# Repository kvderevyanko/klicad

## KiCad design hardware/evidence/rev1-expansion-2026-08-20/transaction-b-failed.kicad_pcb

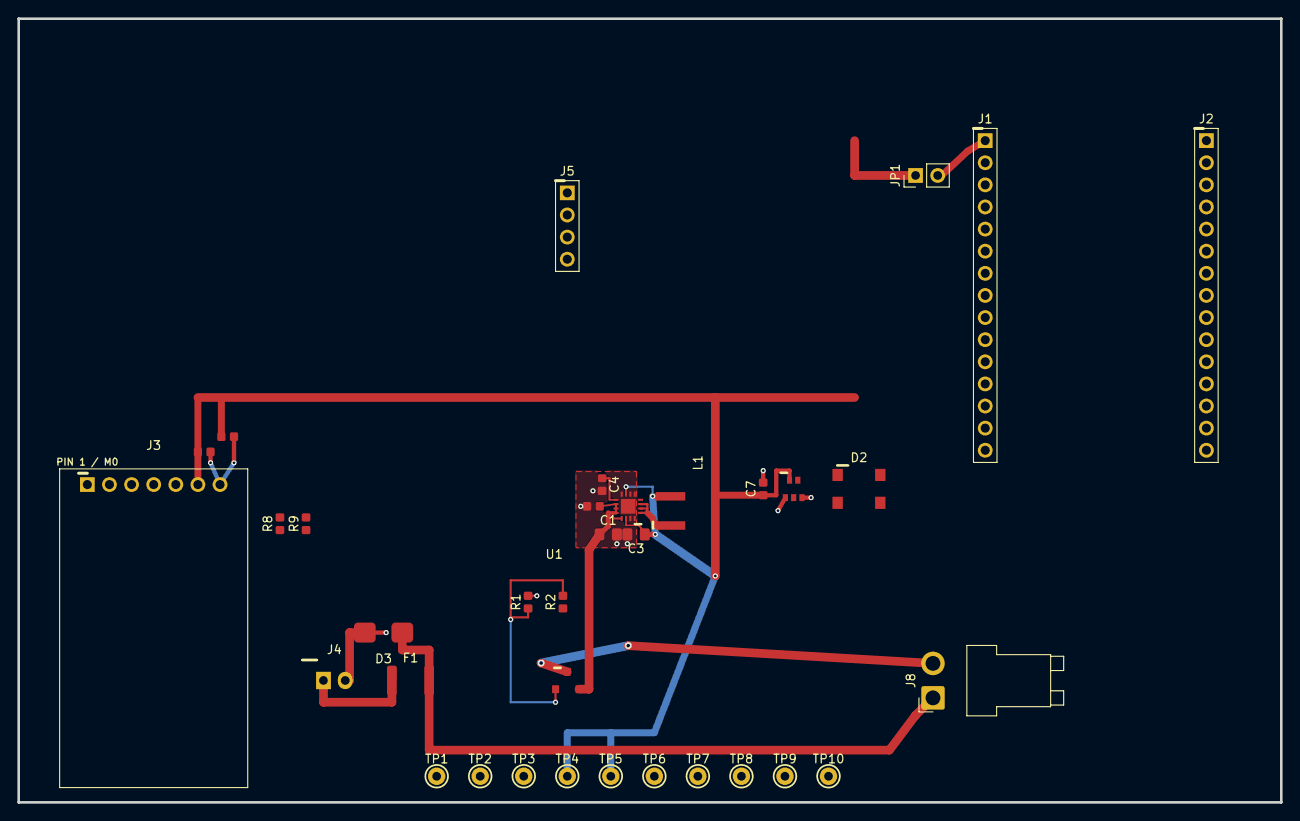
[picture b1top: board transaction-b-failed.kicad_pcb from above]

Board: 2 copper layers, 145.0 x 90.0 mm, 35 parts (0 on the bottom side), 20 nets.

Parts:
C1: GRM21BR61E106KA73; Murata_GRM21_2012Metric
C2, C6, C7: GRM188R71C104KA01D; Murata_GRM188_1608Metric
C3: GRM21BR61A226ME44; Murata_GRM21_2012Metric
C4: GRM1885C1H332JA01D; Murata_GRM188_1608Metric
C5: GRM188R61A106MAAL; Murata_GRM188_1608Metric
D2: WS2812B-V5; WorldSemi_WS2812B-V5_PLACEMENT_CANDIDATE_NOT_RELEASED
D3: SMBJ10CA; Littelfuse_SMBJ10CA_DO214AA
F1: 1812L200/16; Littelfuse_1812L200_16_4532Metric
J1: SSW-115-02-G-S DEVKIT LEFT; Samtec_SSW_1x15_P2.54mm_THT
J2: SSW-115-02-G-S DEVKIT RIGHT; Samtec_SSW_1x15_P2.54mm_THT
J3: E220-400T22D / E220-900T22D SOCKET; E220_T22D_Socket_400_900
J4: B2B-XH-A; JST_B2B-XH-A_1x02_P2.50mm_THT
J5: SSW-104-02-G-S; Samtec_SSW_1x04_P2.54mm_THT
J8: B2PS-VH(LF)(SN); JST_VH_B2PS-VH_1x02_P3.96mm_Horizontal
JP1: TSW-102-07-G-S + SNT-100-BK-G; PinHeader_1x02_P2.54mm_Vertical
L1: XFL4020-222MEB; Coilcraft_XFL4020-222MEB
Q1: DMP3130LQ-7; Diodes_DMP3130LQ-7_SOT23
R1: 100k 1%; Resistor_0603_1608Metric
R2: 1M 1%; Resistor_0603_1608Metric
R8, R9: 10k 1%; Resistor_0603_1608Metric
TP1: BAT_PLUS; TestPoint_THT_1p0mm_PROTOTYPE
TP2: GND; TestPoint_THT_1p0mm_PROTOTYPE
TP3: BUCK_IN; TestPoint_THT_1p0mm_PROTOTYPE
TP4, TP5: 5V_SYS; TestPoint_THT_1p0mm_PROTOTYPE
TP6: E220_M0; TestPoint_THT_1p0mm_PROTOTYPE
TP7: E220_M1; TestPoint_THT_1p0mm_PROTOTYPE
TP8: E220_AUX; TestPoint_THT_1p0mm_PROTOTYPE
TP9: E220_RXD; TestPoint_THT_1p0mm_PROTOTYPE
TP10: E220_TXD; TestPoint_THT_1p0mm_PROTOTYPE
U1: TPS62133RGT; TI_TPS62133RGT_RGT0016C
U3: SN74AHCT1G125DBVR; TI_SN74AHCT1G125DBVR_SOT23-5

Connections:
/5V_SYS: C3.1, C5.1, C6.1, C7.1, D2.1, J3.6, JP1.1, L1.2, TP4.1, TP5.1, U1.7, U1.14, U3.5
/BAT_FUSED: D3.1, F1.2, J8.1
/BAT_PLUS: F1.1, J4.1, TP1.1
/BAT_SW: J8.2, Q1.3
/BUCK_IN: C1.1, C2.1, Q1.2, R2.1, TP3.1, U1.10, U1.11, U1.12, U1.13
/BUCK_SW: L1.1, U1.1, U1.2, U1.3
/DEVKIT_3V3: J2.1, J5.2
/DEVKIT_VIN: J1.1, JP1.2
/E220_AUX: J1.6, J3.5, TP8.1
/E220_M0: J1.8, J3.1, R8.1, TP6.1
/E220_M1: J1.7, J3.2, R9.1, TP7.1
/E220_RXD: J2.7, J3.3, TP9.1
/E220_TXD: J2.6, J3.4, TP10.1
/GND: C1.2, C2.2, C3.2, C4.2, C5.2, C6.2, C7.2, D2.3, D3.2, J1.2, J2.2, J3.7, J4.2, J5.1, R1.2, R8.2, R9.2, TP2.1, U1.5, U1.6, U1.8, U1.15, U1.16, U1.EP, U3.1, U3.3
/OLED_SCL: J2.14, J5.3
/OLED_SDA: J2.11, J5.4
/Q1_GATE: Q1.1, R1.1, R2.2
/SS_TR: C4.1, U1.9
/WS2812_DATA_3V3: J2.5, U3.2
/WS2812_DIN: D2.4, U3.4
